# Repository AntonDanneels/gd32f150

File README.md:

# gd32f150

This is my personal repository for the gd32f150 microcontroller, with selfmade breakout board and peripheral library with the purpose of learning low level bringup.

The gd32f150 is a small & cheap microcontroller from GigaDevice that has USB device support & all other standard peripherals you would expect from a modern ARM mcu.

## Breakout board

A very simple 2-layer PCB is provided in the `breakout` directory.

## Library 

Generic code to use the peripherals is located in the `lib` directory. Current supported features:

| Feature       | State                |
| ------------- | -------------        |
| SPI           | Initial bringup done |
| GPIO          | Initial bringup done |
| RCU           | Initial bringup done |
| RTC           | Initial bringup done |
| PMU           | Initial bringup done |
| EXTI          | Initial bringup done |
| I2C           | WIP                  |
| ADC           | Planned              |
| USB           | Planned              |

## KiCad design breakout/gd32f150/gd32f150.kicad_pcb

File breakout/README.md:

# GD32F150 Breakout board

This very simple 2-layer board exposes all pins of the gd32f150g8 (QFN-28) variant and includes:

- microUSB port
- 5V to 3V3 from the USB connector
- 8 MHz crystal

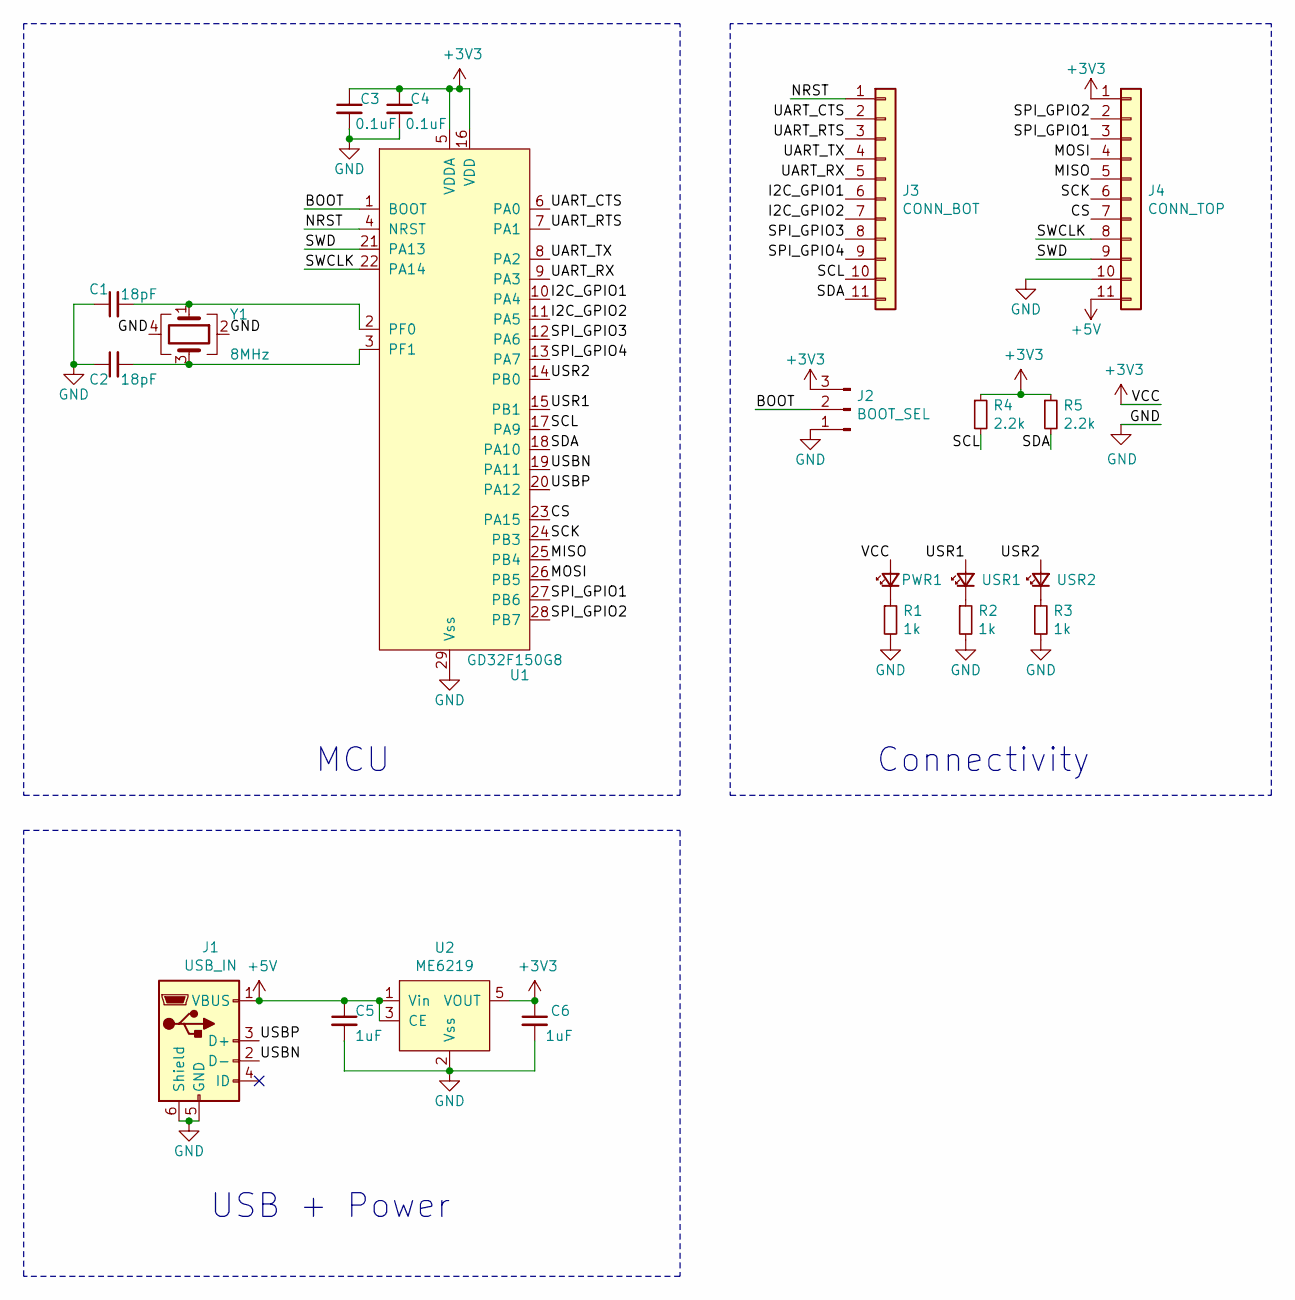
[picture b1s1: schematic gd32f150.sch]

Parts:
C1, C2: 18pF; C_0603_1608Metric_Pad1.08x0.95mm_HandSolder
C3, C4: 0.1uF; C_0603_1608Metric_Pad1.08x0.95mm_HandSolder
C5, C6: 1uF; C_0603_1608Metric_Pad1.08x0.95mm_HandSolder
J1: USB_IN; USB_Micro-B_Amphenol_10118194_Horizontal
J2: BOOT_SEL; PinHeader_1x03_P2.54mm_Vertical
J3: CONN_BOT; PinHeader_1x11_P2.54mm_Vertical
J4: CONN_TOP; PinHeader_1x11_P2.54mm_Vertical
PWR1: PWR; LED_0603_1608Metric_Pad1.05x0.95mm_HandSolder
R1, R2, R3: 1k; R_0603_1608Metric_Pad0.98x0.95mm_HandSolder
R4, R5: 2.2k; R_0603_1608Metric_Pad0.98x0.95mm_HandSolder
U1: GD32F150G8; QFN-28_EP_4x4_Pitch0.4mm
U2: ME6219; SOT-23-5_HandSoldering
USR1, USR2: USR1; LED_0603_1608Metric_Pad1.05x0.95mm_HandSolder
Y1: 8MHz; Crystal_SMD_3225-4Pin_3.2x2.5mm_HandSoldering

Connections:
+3V3: C3.1, C4.1, C6.1, J2.3, J4.1, PWR1.2 (A), R4.1, R5.1, U1.5 (VDDA), U1.16 (VDD), U2.5 (VOUT)
+5V: C5.1, J1.1 (VBUS), J4.11, U2.1 (Vin), U2.3 (CE)
/BOOT: J2.2, U1.1 (BOOT)
/CS: J4.7, U1.23 (PA15)
/I2C_GPIO1: J3.6, U1.10 (PA4)
/I2C_GPIO2: J3.7, U1.11 (PA5)
/MISO: J4.5, U1.25 (PB4)
/MOSI: J4.4, U1.26 (PB5)
/NRST: J3.1, U1.4 (NRST)
/SCK: J4.6, U1.24 (PB3)
/SCL: J3.10, R4.2, U1.17 (PA9)
/SDA: J3.11, R5.2, U1.18 (PA10)
/SPI_GPIO1: J4.3, U1.27 (PB6)
/SPI_GPIO2: J4.2, U1.28 (PB7)
/SPI_GPIO3: J3.8, U1.12 (PA6)
/SPI_GPIO4: J3.9, U1.13 (PA7)
/SWCLK: J4.8, U1.22 (PA14)
/SWD: J4.9, U1.21 (PA13)
/UART_CTS: J3.2, U1.6 (PA0)
/UART_RTS: J3.3, U1.7 (PA1)
/UART_RX: J3.5, U1.9 (PA3)
/UART_TX: J3.4, U1.8 (PA2)
/USBN: J1.2 (D-), U1.19 (PA11)
/USBP: J1.3 (D+), U1.20 (PA12)
/USR1: U1.15 (PB1), USR1.2 (A)
/USR2: U1.14 (PB0), USR2.2 (A)
GND: C1.1, C2.1, C3.2, C4.2, C5.2, C6.2, J1.5 (GND), J1.6 (Shield), J2.1, J4.10, R1.2, R2.2, R3.2, U1.29 (Vss), U2.2 (Vss), Y1.2, Y1.4
unnamed: C1.2, U1.2 (PF0), Y1.1
unnamed: C2.2, U1.3 (PF1), Y1.3
unnamed: PWR1.1 (K), R1.1
unnamed: R2.1, USR1.1 (K)
unnamed: R3.1, USR2.1 (K)

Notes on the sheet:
MCU
USB + Power
Connectivity

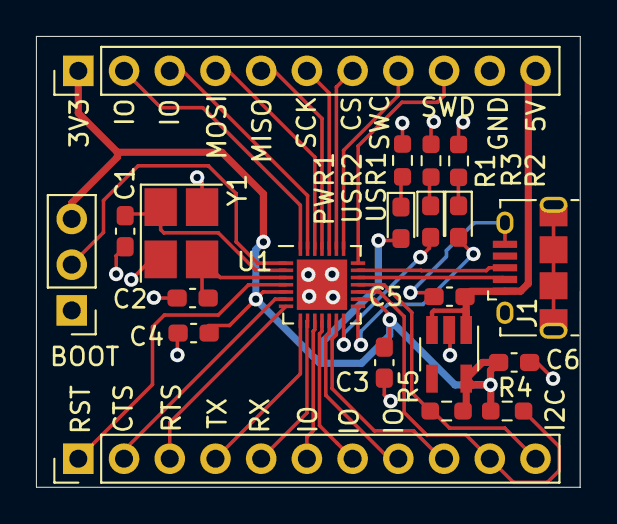
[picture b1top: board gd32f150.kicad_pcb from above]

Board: 2 copper layers, 30.2 x 25.0 mm, 21 parts (0 on the bottom side), 32 nets.

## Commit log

2021-02-27 breakout: add simple breakout board for gd32f150g8
2021-02-27 lib: add initial files for {gpio, systick, spi}
2021-02-27 README: update to explain directories
2021-03-07 lib: systick: add {enable, disable} fns
2021-03-07 lib: add initial impls for {exti, pmu, rcu, rtc}
2021-03-07 README: update to reflect lib update
2021-04-02 gd32f150_i2c: add initial implementation
    Only allow to read/write a single byte for now,
    but extending should be trivial.
